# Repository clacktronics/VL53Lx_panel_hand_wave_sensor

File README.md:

# VL53Lx_panel_hand_wave_sensor
Mount and PCB for hand wave sensor

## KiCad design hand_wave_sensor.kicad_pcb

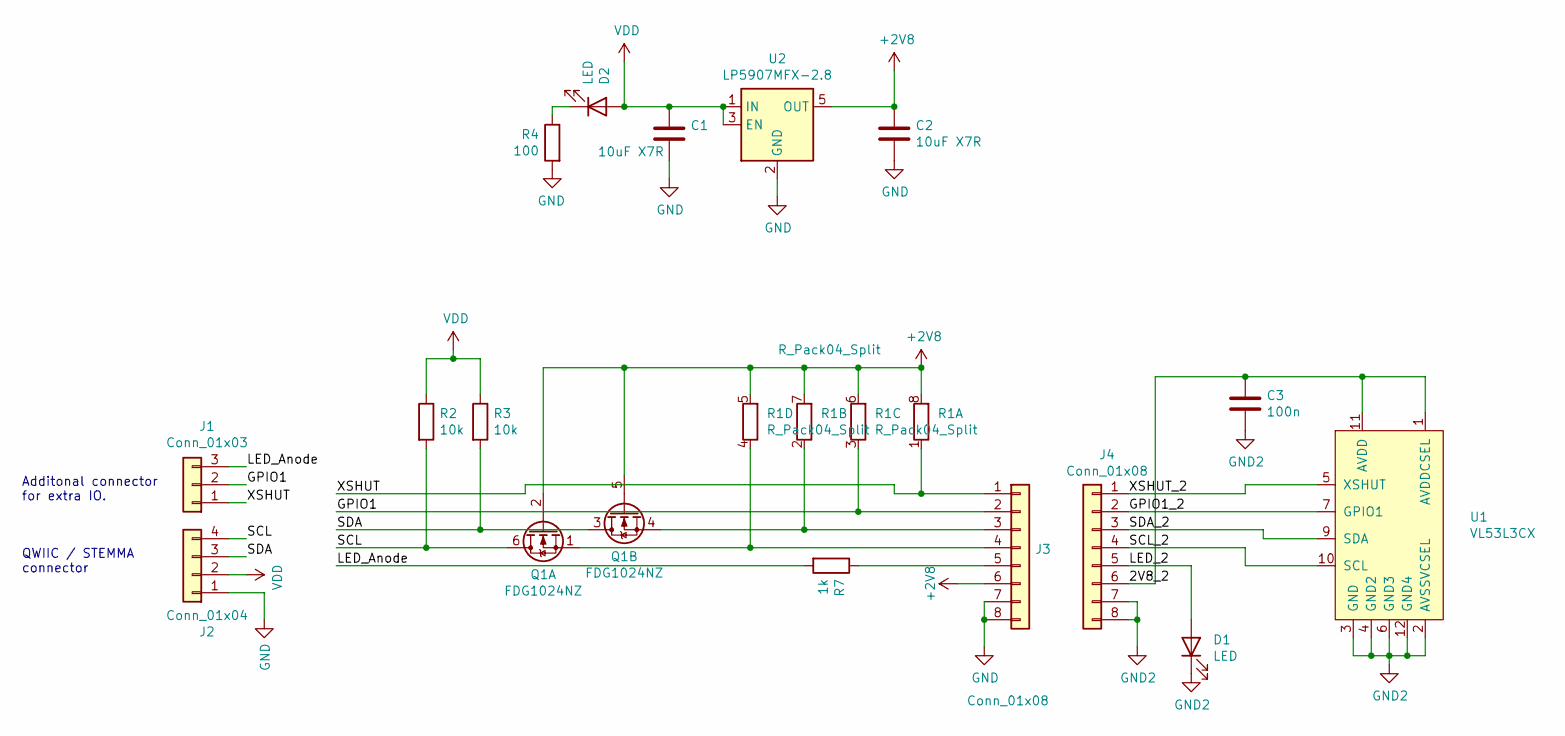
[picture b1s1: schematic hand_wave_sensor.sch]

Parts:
C1, C2: 10uF X7R; C_0402_1005Metric
C3: 100n; C_0402_1005Metric
D1: LED; Wurth SMD LED 156120BS82500
D2: LED; LED_0402_1005Metric
J1: Conn_01x03; JST_SH_SM03B-SRSS-TB_1x03-1MP_P1.00mm_Horizontal
J2: Conn_01x04; JST_SH_SM04B-SRSS-TB_1x04-1MP_P1.00mm_Horizontal
J3: Conn_01x08; PinHeader_1x08_P1.00mm_Vertical
J4: Conn_01x08; 01x08_solder_pad
Q1: FDG1024NZ; SOT-363_SC-70-6
R1: R_Pack04_Split; R_Array_Convex_4x0402
R2, R3: 10k; R_0402_1005Metric
R4: 100; R_0402_1005Metric
R7: 1k; R_0402_1005Metric
U1: VL53L3CX
U2: LP5907MFX-2.8; SOT-23-5

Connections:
+2V8: C2.1, J3.6, Q1.2 (G), Q1.5 (G), R1.5 (R4.2), R1.6 (R3.2), R1.7 (R2.2), R1.8 (R1.2), U2.5 (OUT)
/2V8_2: C3.1, J4.6, U1.1 (AVDDCSEL), U1.11 (AVDD)
/GPIO1: J1.2, J3.2, R1.3 (R3.1)
/GPIO1_2: J4.2, U1.7 (GPIO1)
/LED_2: D1.2 (A), J4.5
/LED_Anode: J1.3, R7.2
/SCL: J2.4, Q1.6 (D), R2.2
/SCL_2: J4.4, U1.10 (SCL)
/SDA: J2.3, Q1.3 (D), R3.2
/SDA_2: J4.3, U1.9 (SDA)
/XSHUT: J1.1, J3.1, R1.1 (R1.1)
/XSHUT_2: J4.1, U1.5 (XSHUT)
GND: C1.2, C2.2, J2.1, J3.7, J3.8, R4.2, U2.2 (GND)
GND2: C3.2, D1.1 (K), J4.7, J4.8, U1.2 (AVSSVCSEL), U1.3 (GND), U1.4 (GND2), U1.6 (GND3), U1.12 (GND4)
unnamed: D2.1 (K), R4.1
unnamed: J3.3, Q1.4 (S), R1.2 (R2.1)
unnamed: J3.4, Q1.1 (S), R1.4 (R4.1)
unnamed: J3.5, R7.1
VDD: C1.1, D2.2 (A), J2.2, R2.1, R3.1, U2.1 (IN), U2.3 (EN)

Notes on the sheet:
Additonal connector for extra IO.
QWIIC / STEMMA connector

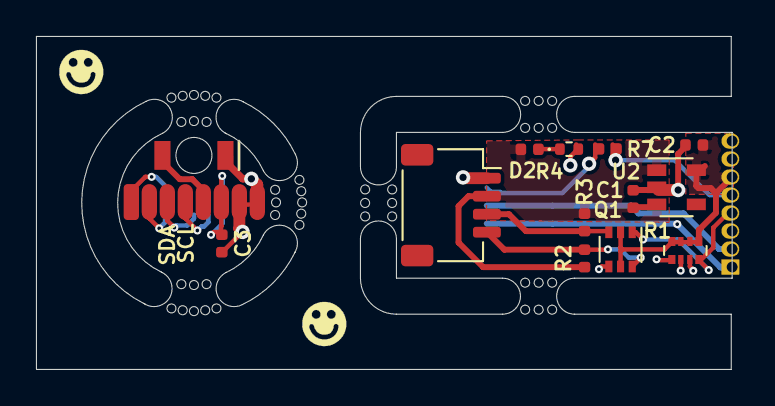
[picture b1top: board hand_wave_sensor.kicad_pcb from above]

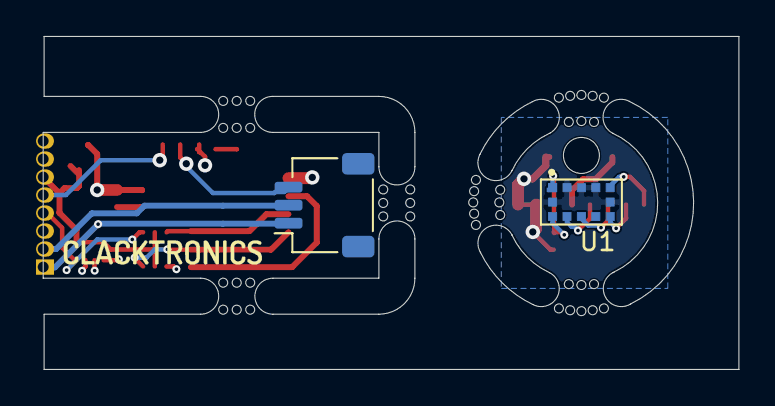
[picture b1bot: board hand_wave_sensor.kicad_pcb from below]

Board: 4 copper layers, 38.7 x 18.5 mm, 23 parts (2 on the bottom side), 19 nets.

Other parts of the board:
mouse-bite-2mm-slot, mouse-bite-2mm-slot#2, mouse-bite-2mm-slot#3: VAL**; mouse-bite-2mm-slot
mouse-bite-2mm-slot#4, mouse-bite-2mm-slot#5, mouse-bite-2mm-slot#6: VAL**; mouse-bite-2mm-slot_8.5mm_disc

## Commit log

2020-12-08 Added PCB files
